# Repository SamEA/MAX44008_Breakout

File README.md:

MAX44008_Breakout
=================

This is a breakout board for Maxim Color Sensor MAX44008

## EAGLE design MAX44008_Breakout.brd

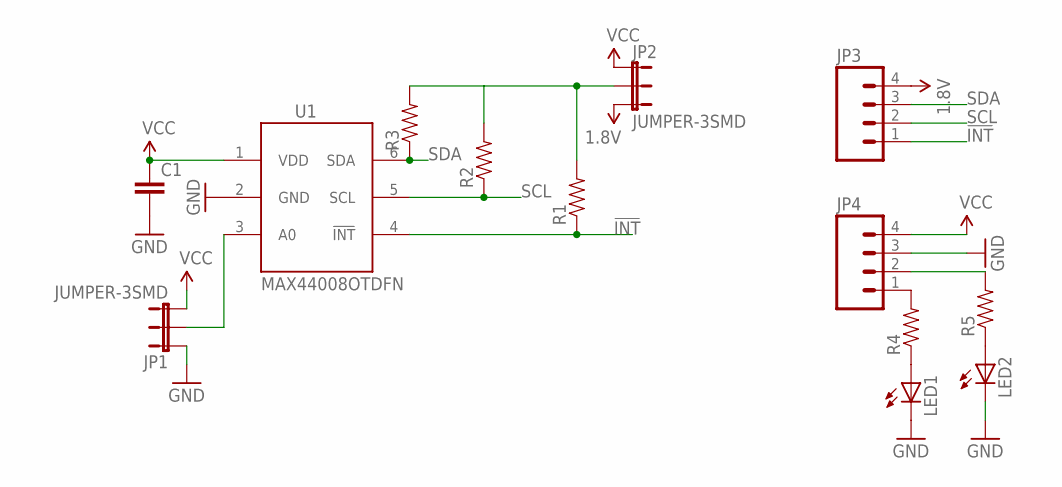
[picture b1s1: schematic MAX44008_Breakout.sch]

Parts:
C1: CAP0603-CAP; 0603-CAP
JP1, JP2: JUMPER-3SMD; SJ_3
JP3, JP4: M04PTH; 1X04
LED1, LED2: LED0603; LED-0603
R1, R2, R3, R4, R5: RESISTOR0603-RES; 0603-RES
U1: MAX44008OTDFN; MAX44008

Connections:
1.8V: JP2.3, JP3.4
!INT: JP3.1, R1.1, U1.4 (!INT)
GND: C1.2, JP1.1, JP4.3, LED1.C, LED2.C, U1.2 (GND)
unnamed: LED1.A, R4.1
unnamed: LED2.A, R5.1
unnamed: JP1.2, U1.3 (A0)
unnamed: JP2.2, R1.2, R2.2, R3.2
unnamed: JP4.2, R5.2
unnamed: JP4.1, R4.2
SCL: JP3.2, R2.1, U1.5 (SCL)
SDA: JP3.3, R3.1, U1.6 (SDA)
VCC: C1.1, JP1.3, JP2.1, JP4.4, U1.1 (VDD)

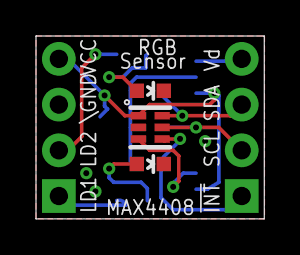
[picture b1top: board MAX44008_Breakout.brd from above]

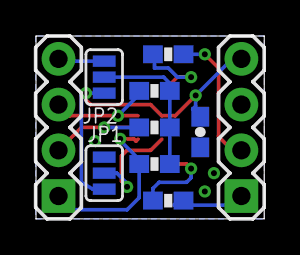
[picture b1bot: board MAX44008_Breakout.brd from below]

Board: 2 copper layers, 12.7 x 10.2 mm, 13 parts (10 on the bottom side), 12 nets.

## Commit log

2013-11-08 Added picture

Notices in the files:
parts and their libraries:
SparkFun-Passives: Licensing: CC v3.0 Share-Alike You are welcome to use this library for commercial purposes.
